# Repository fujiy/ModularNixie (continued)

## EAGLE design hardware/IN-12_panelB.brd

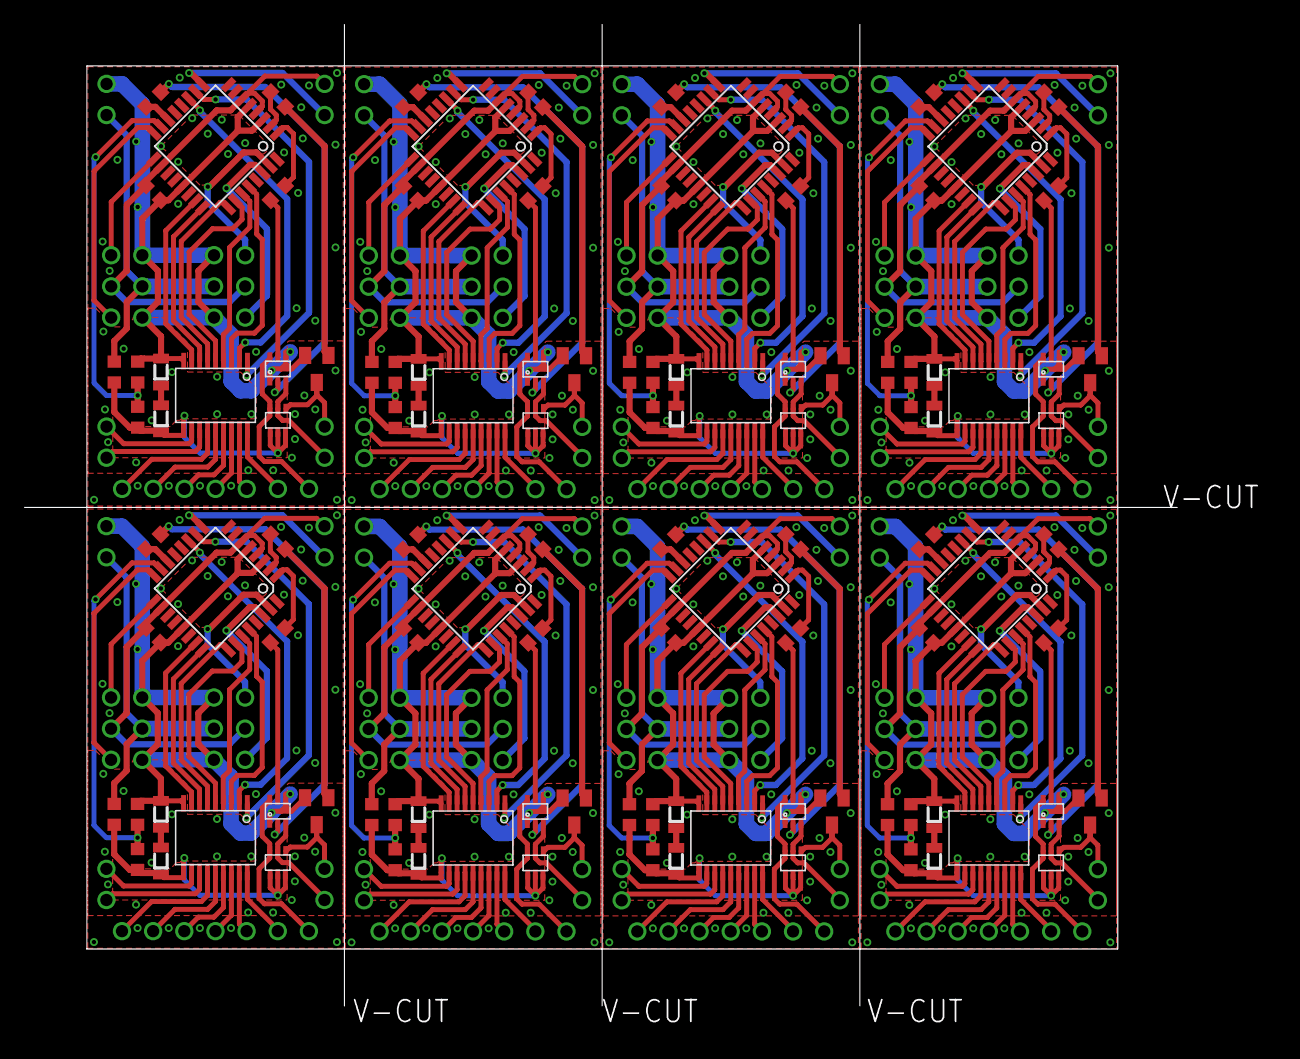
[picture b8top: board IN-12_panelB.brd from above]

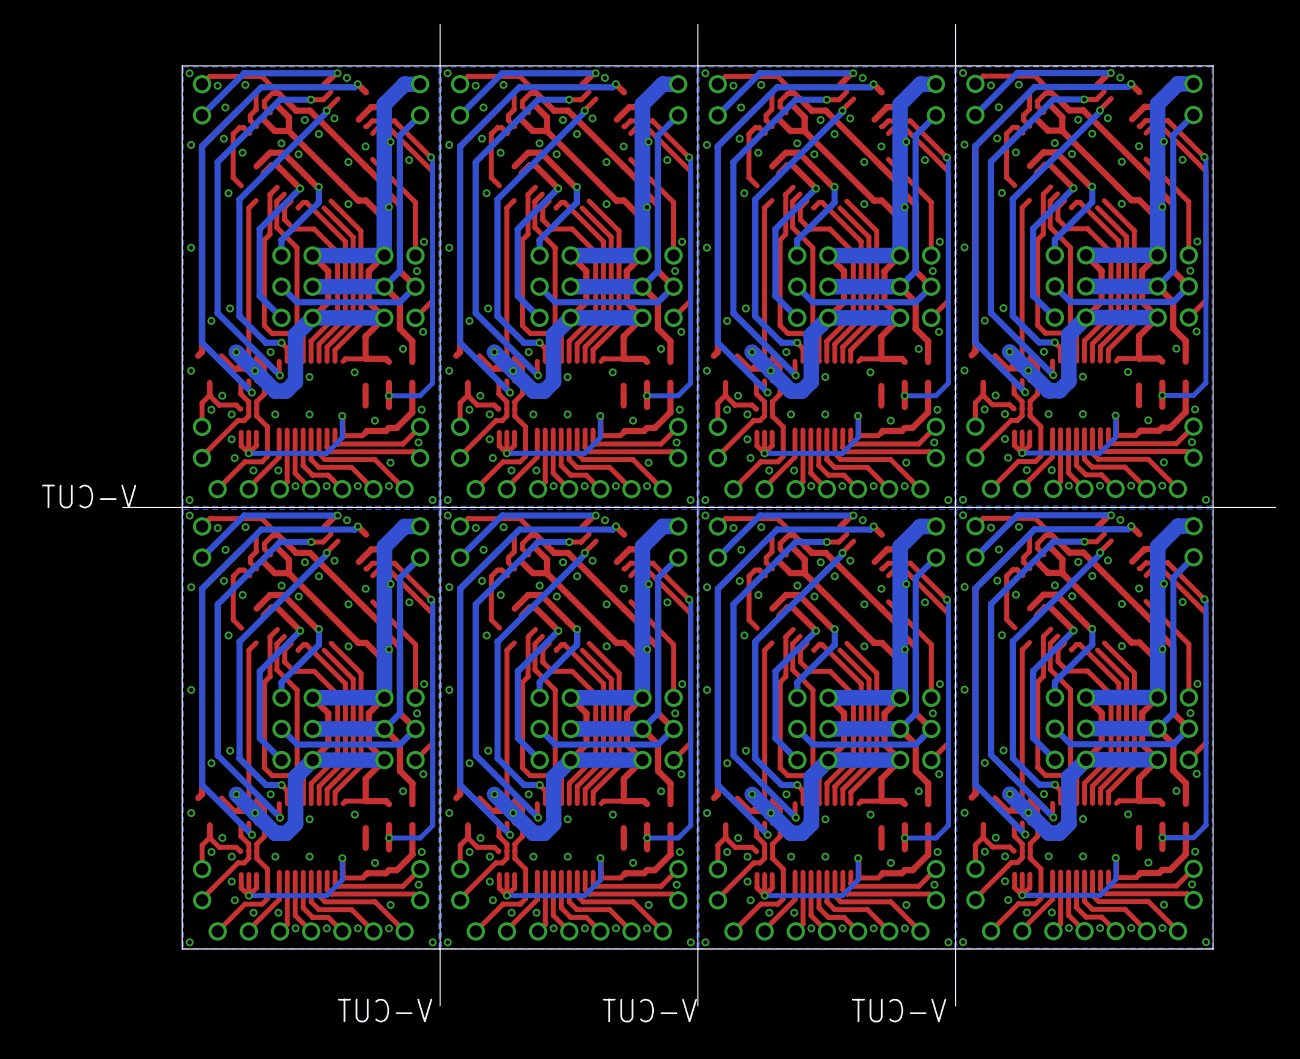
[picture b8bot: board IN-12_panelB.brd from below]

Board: 2 copper layers, 94.0 x 80.0 mm, 128 parts (8 on the bottom side), 216 nets.

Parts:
ATMEGA1, ATMEGA2, ATMEGA3, ATMEGA4, ATMEGA5, ATMEGA6, ATMEGA7, ATMEGA48: ATMEGA48/88/168-AU; TQFP32-08
C1, C2, C3, C4, C5, C6, C7, C8: 0.1µF; C0603
D1, D4, D7, D10, D13, D16, D19, D22: 36V; S-MINI-2P
D2, D5, D8, D11, D14, D17, D20, D23: 12V; S-MINI-2P
D3, D6, D9, D12, D15, D18, D21, D24: MA6Z121; SMINI6-F1
L, L1, L2, L3, L4, L5, L6, L7: P2_3_2.54S
Q1, Q2, Q3, Q4, Q5, Q6, Q7, Q8: HN1C01FU; SOT-363
R, R2, R14, R21, R28, R35, R42, R49: P2_3_2.54SF
R1, R3, R8, R9, R15, R16, R22, R23, R29, R30, R36, R37, R43, R44, R50, R51: 1M; R0603
R4, R10, R17, R24, R31, R38, R45, R52: 100k; R0603
R5, R6, R7, R11, R12, R13, R18, R19, R20, R25, R26, R27, R32, R33, R34, R39, R40, R41, R46, R47, R48, R53, R54, R55: 10k; R0603
T1, T3, T5, T7, T9, T11, T13, T15: TD62083AFNG; SSOP18-P-225-0.65
T2, T4, T6, T8, T10, T12, T14, T16: BC846; SOT23

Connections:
GND: ATMEGA48.3, ATMEGA48.5, ATMEGA48.21, C1.2, D2.1, L.4, L.6, Q1.1, Q1.4, R.4, R.6, R4.1, T1.P9, T2.2
GND1: ATMEGA1.3, ATMEGA1.5, ATMEGA1.21, C2.2, D5.1, L1.4, L1.6, Q2.1, Q2.4, R2.4, R2.6, R10.1, T3.P9, T4.2
GND2: ATMEGA2.3, ATMEGA2.5, ATMEGA2.21, C3.2, D8.1, L2.4, L2.6, Q3.1, Q3.4, R14.4, R14.6, R17.1, T5.P9, T6.2
GND3: ATMEGA3.3, ATMEGA3.5, ATMEGA3.21, C4.2, D11.1, L3.4, L3.6, Q4.1, Q4.4, R21.4, R21.6, R24.1, T7.P9, T8.2
GND4: ATMEGA4.3, ATMEGA4.5, ATMEGA4.21, C5.2, D14.1, L4.4, L4.6, Q5.1, Q5.4, R28.4, R28.6, R31.1, T9.P9, T10.2
GND5: ATMEGA5.3, ATMEGA5.5, ATMEGA5.21, C6.2, D17.1, L5.4, L5.6, Q6.1, Q6.4, R35.4, R35.6, R38.1, T11.P9, T12.2
GND6: ATMEGA6.3, ATMEGA6.5, ATMEGA6.21, C7.2, D20.1, L6.4, L6.6, Q7.1, Q7.4, R42.4, R42.6, R45.1, T13.P9, T14.2
GND7: ATMEGA7.3, ATMEGA7.5, ATMEGA7.21, C8.2, D23.1, L7.4, L7.6, Q8.1, Q8.4, R49.4, R49.6, R52.1, T15.P9, T16.2
K3: D3.P3, Q1.6
K8: D3.P2, Q1.3
K12: D6.P2, Q2.3
K17: D6.P3, Q2.6
K22: D9.P2, Q3.3
K27: D9.P3, Q3.6
K32: D12.P2, Q4.3
K37: D12.P3, Q4.6
K42: D15.P2, Q5.3
K47: D15.P3, Q5.6
K52: D18.P2, Q6.3
K57: D18.P3, Q6.6
K62: D21.P2, Q7.3
K67: D21.P3, Q7.6
K72: D24.P2, Q8.3
K77: D24.P3, Q8.6
KD: D3.P1, T2.3
KD1: D6.P1, T4.3
KD2: D9.P1, T6.3
KD3: D12.P1, T8.3
KD4: D15.P1, T10.3
KD5: D18.P1, T12.3
KD6: D21.P1, T14.3
KD7: D24.P1, T16.3
L_RX: ATMEGA48.17, L.1
L_RX1: ATMEGA1.17, L1.1
L_RX2: ATMEGA2.17, L2.1
L_RX3: ATMEGA3.17, L3.1
L_RX4: ATMEGA4.17, L4.1
L_RX5: ATMEGA5.17, L5.1
L_RX6: ATMEGA6.17, L6.1
L_RX7: ATMEGA7.17, L7.1
L_TX: ATMEGA48.16, L.3
L_TX1: ATMEGA1.16, L1.3
L_TX2: ATMEGA2.16, L2.3
L_TX3: ATMEGA3.16, L3.3
L_TX4: ATMEGA4.16, L4.3
L_TX5: ATMEGA5.16, L5.3
L_TX6: ATMEGA6.16, L6.3
L_TX7: ATMEGA7.16, L7.3
N0: ATMEGA48.10, T1.P1
N1: ATMEGA48.27, T1.P4
N2: ATMEGA48.26, T1.P5
N3: ATMEGA48.14, R7.1
N4: ATMEGA48.25, T1.P6
N5: ATMEGA48.24, T1.P7
N6: ATMEGA48.23, T1.P8
N7: ATMEGA48.28, T1.P3
N8: ATMEGA48.1, R6.1
N9: ATMEGA48.11, T1.P2
N10: ATMEGA1.23, T3.P8
N11: ATMEGA1.24, T3.P7
N12: ATMEGA1.26, T3.P5
N13: ATMEGA1.27, T3.P4
N14: ATMEGA1.28, T3.P3
N15: ATMEGA1.11, T3.P2
N16: ATMEGA1.10, T3.P1
N17: ATMEGA1.25, T3.P6
N18: ATMEGA1.1, R12.1
N19: ATMEGA1.14, R13.1
N20: ATMEGA2.23, T5.P8
N21: ATMEGA2.24, T5.P7
N22: ATMEGA2.26, T5.P5
N23: ATMEGA2.27, T5.P4
N24: ATMEGA2.28, T5.P3
N25: ATMEGA2.11, T5.P2
N26: ATMEGA2.10, T5.P1
N27: ATMEGA2.25, T5.P6
N28: ATMEGA2.1, R19.1
N29: ATMEGA2.14, R20.1
N30: ATMEGA3.23, T7.P8
N31: ATMEGA3.24, T7.P7
N32: ATMEGA3.26, T7.P5
N33: ATMEGA3.27, T7.P4
N34: ATMEGA3.28, T7.P3
N35: ATMEGA3.11, T7.P2
N36: ATMEGA3.10, T7.P1
N37: ATMEGA3.25, T7.P6
N38: ATMEGA3.1, R26.1
N39: ATMEGA3.14, R27.1
N40: ATMEGA4.23, T9.P8
N41: ATMEGA4.24, T9.P7
N42: ATMEGA4.26, T9.P5
N43: ATMEGA4.27, T9.P4
N44: ATMEGA4.28, T9.P3
N45: ATMEGA4.11, T9.P2
N46: ATMEGA4.10, T9.P1
N47: ATMEGA4.25, T9.P6
N48: ATMEGA4.1, R33.1
N49: ATMEGA4.14, R34.1
N50: ATMEGA5.23, T11.P8
N51: ATMEGA5.24, T11.P7
N52: ATMEGA5.26, T11.P5
N53: ATMEGA5.27, T11.P4
N54: ATMEGA5.28, T11.P3
N55: ATMEGA5.11, T11.P2
N56: ATMEGA5.10, T11.P1
N57: ATMEGA5.25, T11.P6
N58: ATMEGA5.1, R40.1
N59: ATMEGA5.14, R41.1
N60: ATMEGA6.23, T13.P8
N61: ATMEGA6.24, T13.P7
N62: ATMEGA6.26, T13.P5
N63: ATMEGA6.27, T13.P4
N64: ATMEGA6.28, T13.P3
N65: ATMEGA6.11, T13.P2
N66: ATMEGA6.10, T13.P1
N67: ATMEGA6.25, T13.P6
N68: ATMEGA6.1, R47.1
N69: ATMEGA6.14, R48.1
N70: ATMEGA7.23, T15.P8
N71: ATMEGA7.24, T15.P7
N72: ATMEGA7.26, T15.P5
N73: ATMEGA7.27, T15.P4
N74: ATMEGA7.28, T15.P3
N75: ATMEGA7.11, T15.P2
N76: ATMEGA7.10, T15.P1
N77: ATMEGA7.25, T15.P6
N78: ATMEGA7.1, R54.1
N79: ATMEGA7.14, R55.1
unnamed: D1.1, D2.2
unnamed: D1.2, D3.P4, D3.P5, D3.P6, R1.1, R3.2, T1.P10
unnamed: D4.1, D5.2
unnamed: D4.2, D6.P4, D6.P5, D6.P6, R8.1, R9.2, T3.P10
unnamed: Q2.2, R13.2
unnamed: Q2.5, R12.2
unnamed: R11.2, T4.1
unnamed: D7.1, D8.2
unnamed: D7.2, D9.P4, D9.P5, D9.P6, R15.1, R16.2, T5.P10
unnamed: Q3.2, R20.2
unnamed: Q3.5, R19.2
unnamed: Q1.2, R7.2
unnamed: R18.2, T6.1
unnamed: Q1.5, R6.2
unnamed: R5.2, T2.1
unnamed: D10.1, D11.2
unnamed: D10.2, D12.P4, D12.P5, D12.P6, R22.1, R23.2, T7.P10
unnamed: Q4.2, R27.2
unnamed: Q4.5, R26.2
unnamed: R25.2, T8.1
unnamed: D13.1, D14.2
unnamed: D13.2, D15.P4, D15.P5, D15.P6, R29.1, R30.2, T9.P10
unnamed: Q5.2, R34.2
unnamed: Q5.5, R33.2
unnamed: R32.2, T10.1
unnamed: D16.1, D17.2
unnamed: D16.2, D18.P4, D18.P5, D18.P6, R36.1, R37.2, T11.P10
unnamed: Q6.2, R41.2
unnamed: Q6.5, R40.2
unnamed: R39.2, T12.1
unnamed: D19.1, D20.2
unnamed: D19.2, D21.P4, D21.P5, D21.P6, R43.1, R44.2, T13.P10
unnamed: Q7.2, R48.2
unnamed: Q7.5, R47.2
unnamed: R46.2, T14.1
unnamed: D22.1, D23.2
unnamed: D22.2, D24.P4, D24.P5, D24.P6, R50.1, R51.2, T15.P10
unnamed: Q8.2, R55.2
unnamed: Q8.5, R54.2
unnamed: R53.2, T16.1
ND: ATMEGA48.2, R5.1
ND1: ATMEGA1.2, R11.1
ND2: ATMEGA2.2, R18.1
ND3: ATMEGA3.2, R25.1
ND4: ATMEGA4.2, R32.1
ND5: ATMEGA5.2, R39.1
ND6: ATMEGA6.2, R46.1
ND7: ATMEGA7.2, R53.1
R_RX: ATMEGA48.30, R.3
R_RX1: ATMEGA1.30, R2.3
R_RX2: ATMEGA2.30, R14.3
R_RX3: ATMEGA3.30, R21.3
R_RX4: ATMEGA4.30, R28.3
R_RX5: ATMEGA5.30, R35.3
R_RX6: ATMEGA6.30, R42.3
R_RX7: ATMEGA7.30, R49.3
R_TX: ATMEGA48.31, R.1
R_TX1: ATMEGA1.31, R2.1
R_TX2: ATMEGA2.31, R14.1
R_TX3: ATMEGA3.31, R21.1
R_TX4: ATMEGA4.31, R28.1
R_TX5: ATMEGA5.31, R35.1
R_TX6: ATMEGA6.31, R42.1
R_TX7: ATMEGA7.31, R49.1
SV: ATMEGA48.15, R3.1, R4.2
SV1: ATMEGA1.15, R9.1, R10.2
SV2: ATMEGA2.15, R16.1, R17.2
SV3: ATMEGA3.15, R23.1, R24.2
SV4: ATMEGA4.15, R30.1, R31.2
SV5: ATMEGA5.15, R37.1, R38.2
SV6: ATMEGA6.15, R44.1, R45.2
SV7: ATMEGA7.15, R51.1, R52.2
VCC: ATMEGA48.4, ATMEGA48.6, ATMEGA48.18, C1.1, L.2, R.2
VCC1: ATMEGA1.4, ATMEGA1.6, ATMEGA1.18, C2.1, L1.2, R2.2
VCC2: ATMEGA2.4, ATMEGA2.6, ATMEGA2.18, C3.1, L2.2, R14.2
VCC3: ATMEGA3.4, ATMEGA3.6, ATMEGA3.18, C4.1, L3.2, R21.2
VCC4: ATMEGA4.4, ATMEGA4.6, ATMEGA4.18, C5.1, L4.2, R28.2
VCC5: ATMEGA5.4, ATMEGA5.6, ATMEGA5.18, C6.1, L5.2, R35.2
VCC6: ATMEGA6.4, ATMEGA6.6, ATMEGA6.18, C7.1, L6.2, R42.2
VCC7: ATMEGA7.4, ATMEGA7.6, ATMEGA7.18, C8.1, L7.2, R49.2
VPP: L.5, R.5, R1.2
VPP1: L1.5, R2.5, R8.2
VPP2: L2.5, R14.5, R15.2
VPP3: L3.5, R21.5, R22.2
VPP4: L4.5, R28.5, R29.2
VPP5: L5.5, R35.5, R36.2
VPP6: L6.5, R42.5, R43.2
VPP7: L7.5, R49.5, R50.2

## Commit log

2020-12-09 Init
2020-12-17 Update BOM
